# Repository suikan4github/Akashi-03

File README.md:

# Akashi-03
Nucleo-G431RB test jig.

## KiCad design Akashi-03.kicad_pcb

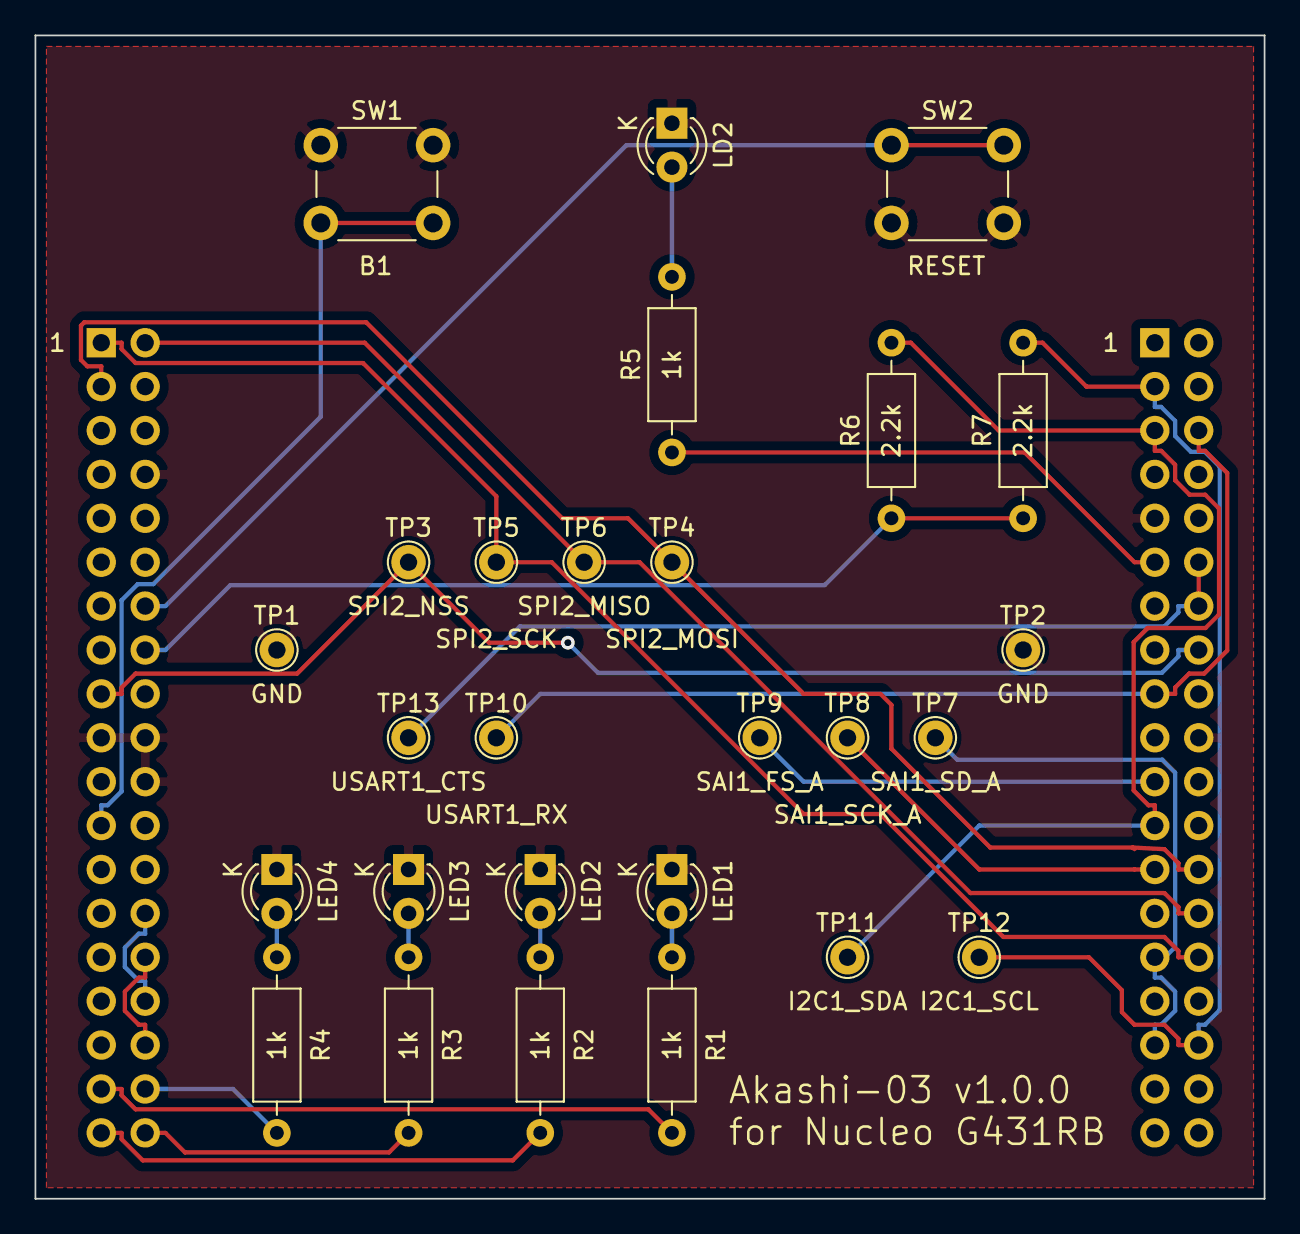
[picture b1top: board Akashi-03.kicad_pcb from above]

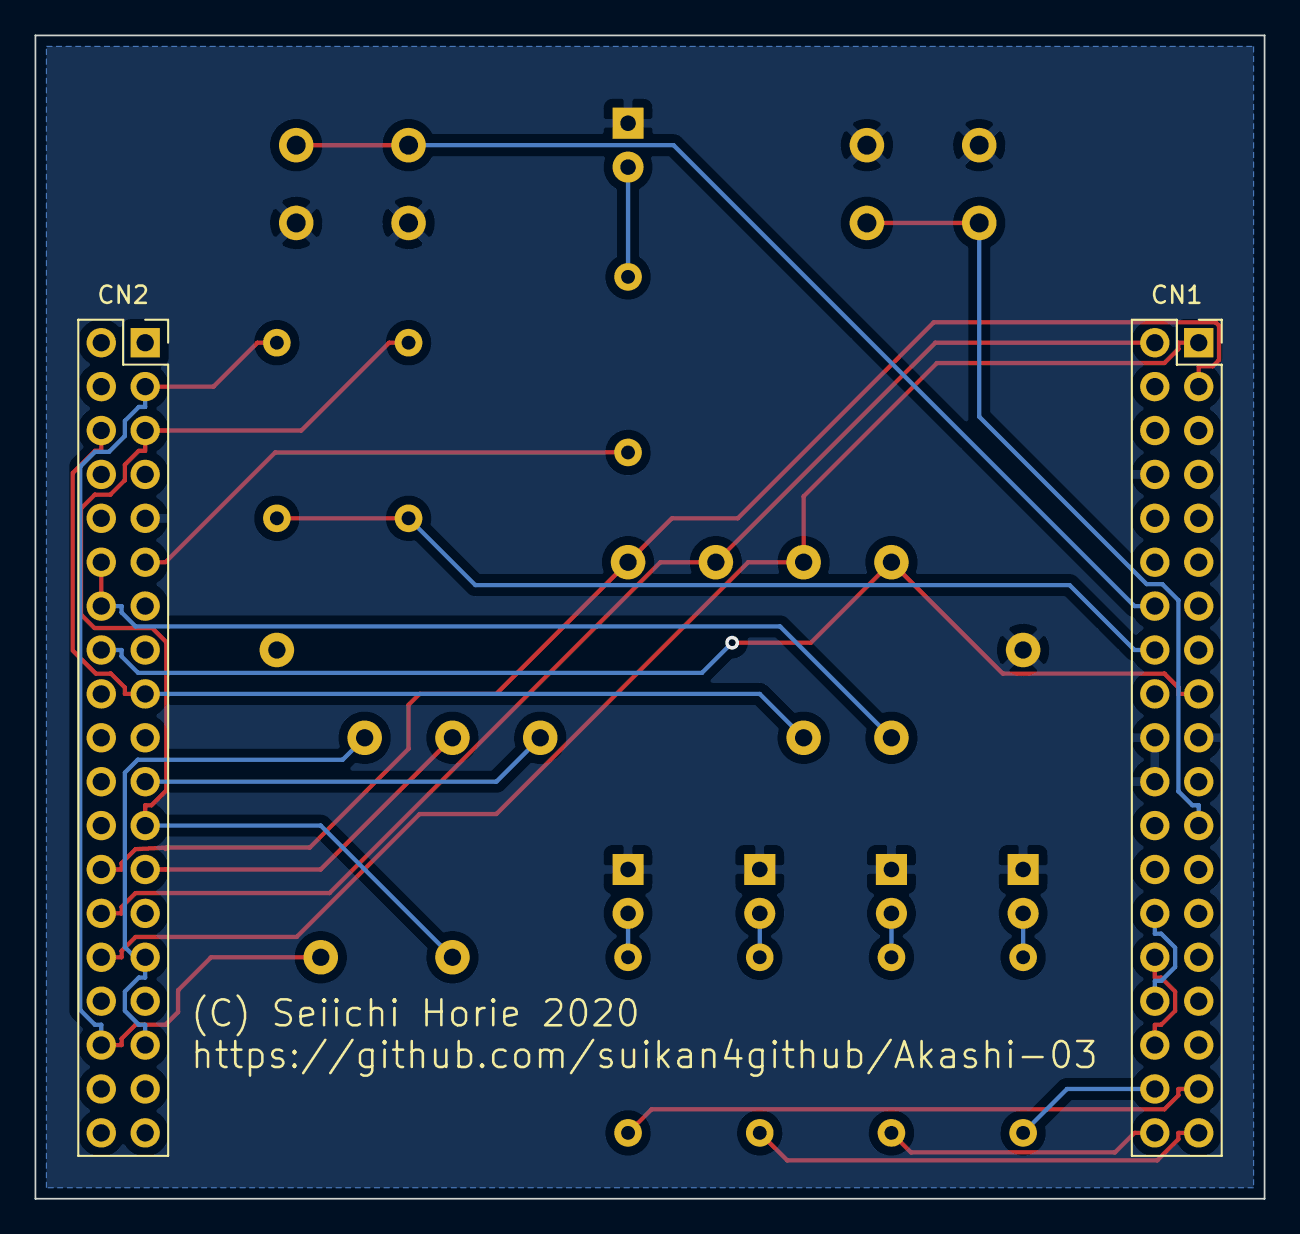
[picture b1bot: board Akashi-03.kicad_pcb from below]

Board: 2 copper layers, 71.1 x 67.3 mm, 29 parts (2 on the bottom side), 27 nets.

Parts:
CN1, CN2: PPPC192LFBN-RC; PinSocket_2x19_P2.54mm_Vertical
LD2: LED; LED_D3.0mm_Clear
LED1, LED2, LED3, LED4: LED; LED_D3.0mm_Clear
R1, R2, R3, R4, R5: 1k; R_Axial_DIN0207_L6.3mm_D2.5mm_P10.16mm_Horizontal
R6, R7: 2.2k; R_Axial_DIN0207_L6.3mm_D2.5mm_P10.16mm_Horizontal
SW1, SW2: SW_Push; SW_PUSH_6mm_H5mm
TP1, TP2, TP3, TP4, TP5, TP6, TP7, TP8, TP9, TP10, TP11, TP12, TP13: GND; TestPoint_THTPad_D2.0mm_Drill1.0mm

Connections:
+3V3: CN1.16, R6.1, R7.1
/B1: CN1.23, SW1.2
/CH1_CTL: CN1.28, CN1.32
/CH2_CTL: CN1.30, CN1.34
/I2C1_SCL: CN2.3, CN2.34, R7.2, TP12.1
/I2C1_SDA: CN2.5, CN2.23, R6.2, TP11.1
/LD2: CN2.11, R5.1
/LED1: CN1.35, R1.1
/LED2: CN1.37, R2.1
/LED3: CN1.38, R3.1
/LED4: CN1.36, R4.1
/SAI1_FS_A: CN2.21, TP9.1
/SAI1_SCK_A: CN2.25, TP8.1
/SAI1_SD_A: CN2.29, CN2.33, TP7.1
/SPI2_MISO: CN1.2, CN2.28, TP6.1
/SPI2_MOSI: CN1.3, CN2.26, TP4.1
/SPI2_NSS: CN1.17, CN2.16, TP3.1
/SPI2_SCK: CN1.1, CN2.30, TP5.1
/USART1_CTS: CN2.12, CN2.14, TP13.1
/USART1_RX: CN2.6, CN2.17, TP10.1
/nRESET: CN1.14, SW2.1
GND: CN1.8, CN1.19, CN1.20, CN1.22, CN2.9, CN2.20, LD2.1, LED1.1, LED2.1, LED3.1, LED4.1, SW1.1, SW2.2, TP1.1, TP2.1
unnamed: LD2.2, R5.2
unnamed: LED1.2, R1.2
unnamed: LED2.2, R2.2
unnamed: LED3.2, R3.2
unnamed: LED4.2, R4.2

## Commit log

2019-04-17 Added changelog
2019-05-12 Added work result
2019-12-11 Deleted all files
2019-12-11 Copied files from Akashi02
2019-12-11 Renamed from Akashi02 to Akashi03
2020-02-15 Added Akashi 03 based on Akashi 01
    The Nucleo G431RB test jig.
2020-02-16 Complete the schematics.
2020-02-16 Document modified.
